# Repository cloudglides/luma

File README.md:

# Luma
It is a 75% layout, mechanical keyboard!  

I made this project because I wanna checkout how matrixs work. This would be my first keyboard!

### PCB
The PCB is designed to be compatible with Cherry MX switches and features hot-swappable kalih sockets.
| Schematics |
| --- |
| | 

| PCB (All Layers)|
| --- |
|  |

## Case

The case is designed to be 3D printed!

| Case top view|
| --- |
|  |

| Case bottom View|
| --- |
|  |

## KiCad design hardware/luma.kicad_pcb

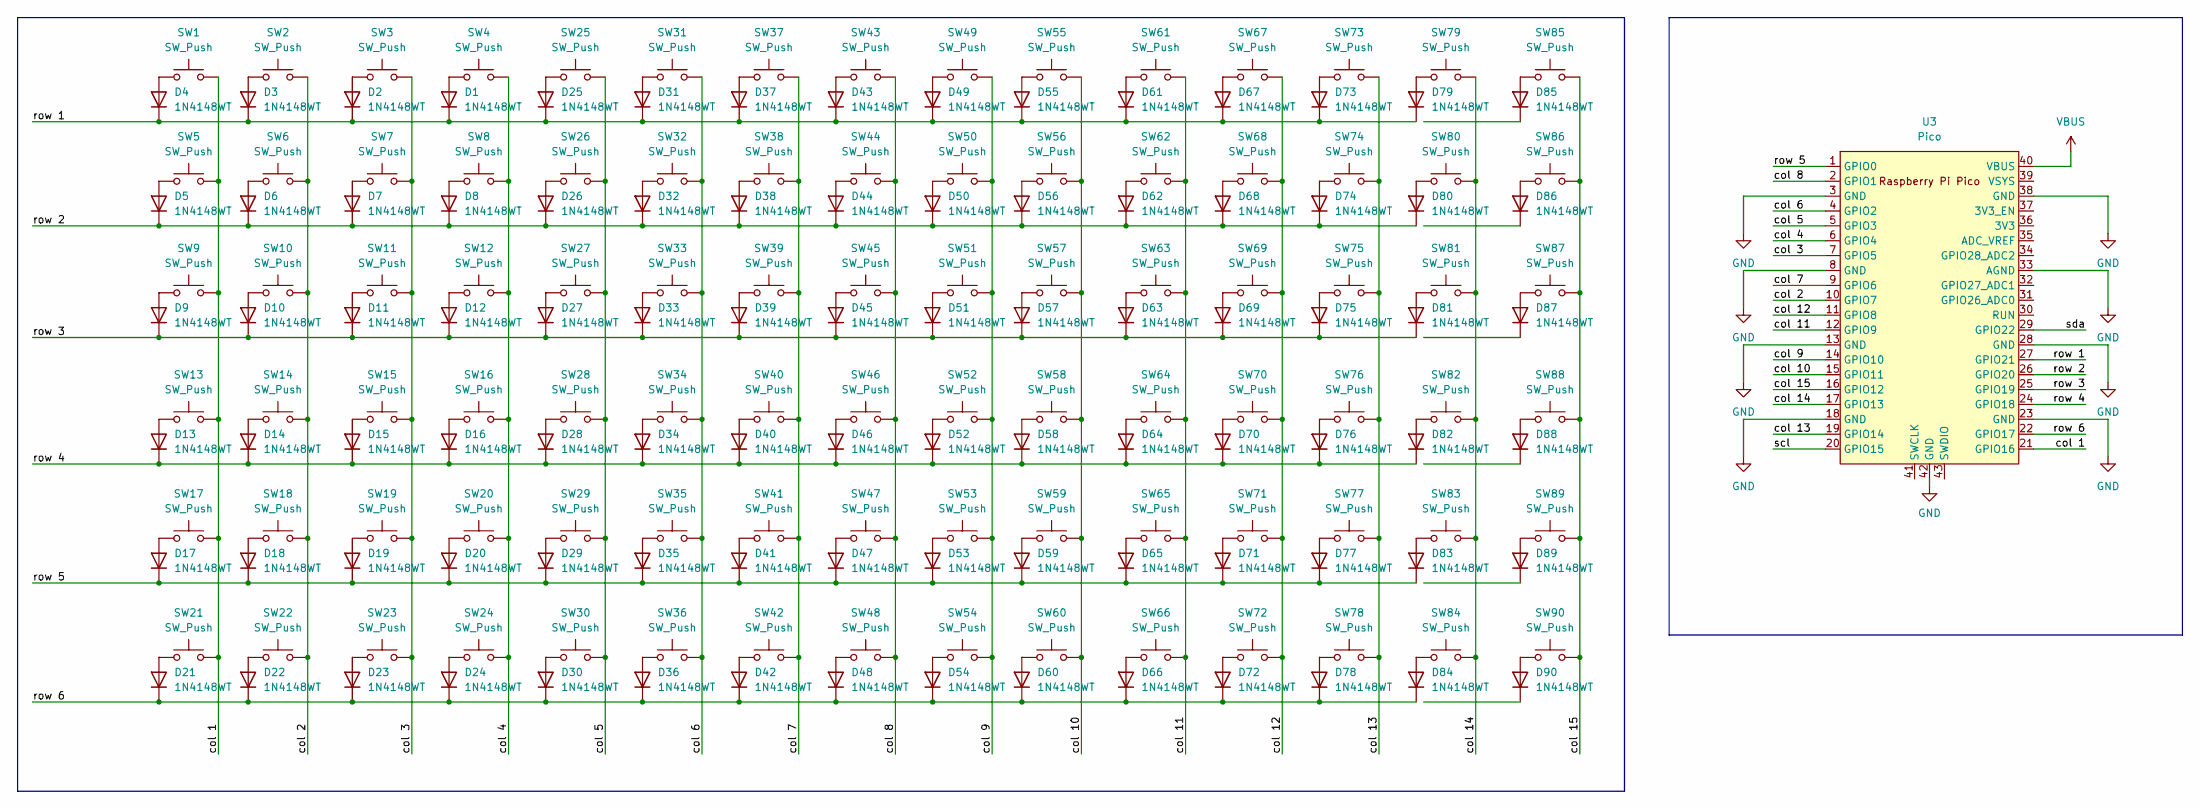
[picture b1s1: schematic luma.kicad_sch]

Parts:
D1, D2, D3, D4, D5, D6, D7, D8, D9, D10, D11, D12, D13, D14, D15, D16, D17, D18, D19, D20, D21, D22, D23, D24, D25, D26, D27, D28, D29, D30, D31, D32, D33, D34, D35, D36, D37, D38, D39, D40, D41, D42, D43, D44, D45, D46, D47, D48, D49, D50, D51, D52, D53, D54, D55, D56, D57, D58, D59, D60, D61, D62, D63, D64, D65, D66, D67, D68, D69, D70, D71, D72, D73, D74, D75, D76, D77, D78, D79, D80, D81, D82, D83, D84, D85, D86, D87, D88, D89, D90: 1N4148WT; D_SOD-523
SW1, SW2, SW3, SW4, SW5, SW6, SW7, SW8, SW9, SW10, SW11, SW12, SW13, SW14, SW15, SW16, SW17, SW18, SW19, SW20, SW21, SW22, SW23, SW24, SW25, SW26, SW27, SW28, SW29, SW31, SW32, SW33, SW34, SW35, SW36, SW37, SW38, SW39, SW40, SW41, SW42, SW43, SW44, SW45, SW46, SW47, SW48, SW49, SW50, SW51, SW52, SW53, SW54, SW55, SW56, SW57, SW58, SW60, SW62, SW63, SW64, SW65, SW66, SW67, SW68, SW69, SW70, SW71, SW72, SW73, SW74, SW75, SW76, SW77, SW79, SW80, SW81, SW82, SW83, SW84, SW85, SW86, SW87, SW88, SW89, SW90: SW_Push; SW_Cherry_MX_1.00u_PCB
SW30, SW59, SW61: SW_Push; SW_Cherry_MX_2.00u_PCB
SW78: SW_Push; SW_Cherry_MX_6.25u_PCB
U3: Pico; RPi_Pico_SMD_TH

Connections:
/col 1: SW1.2, SW5.2, SW9.2, SW13.2, SW17.2, SW21.2, U3.21 (GPIO16)
/col 2: SW2.2, SW6.2, SW10.2, SW14.2, SW18.2, SW22.2, U3.10 (GPIO7)
/col 3: SW3.2, SW7.2, SW11.2, SW15.2, SW19.2, SW23.2, U3.7 (GPIO5)
/col 4: SW4.2, SW8.2, SW12.2, SW16.2, SW20.2, SW24.2, U3.6 (GPIO4)
/col 5: SW25.2, SW26.2, SW27.2, SW28.2, SW29.2, SW30.2, U3.5 (GPIO3)
/col 6: SW31.2, SW32.2, SW33.2, SW34.2, SW35.2, SW36.2, U3.4 (GPIO2)
/col 7: SW37.2, SW38.2, SW39.2, SW40.2, SW41.2, SW42.2, U3.9 (GPIO6)
/col 8: SW43.2, SW44.2, SW45.2, SW46.2, SW47.2, SW48.2, U3.2 (GPIO1)
/col 9: SW49.2, SW50.2, SW51.2, SW52.2, SW53.2, SW54.2, U3.14 (GPIO10)
/col 10: SW55.2, SW56.2, SW57.2, SW58.2, SW59.2, SW60.2, U3.15 (GPIO11)
/col 11: SW61.2, SW62.2, SW63.2, SW64.2, SW65.2, SW66.2, U3.12 (GPIO9)
/col 12: SW67.2, SW68.2, SW69.2, SW70.2, SW71.2, SW72.2, U3.11 (GPIO8)
/col 13: SW73.2, SW74.2, SW75.2, SW76.2, SW77.2, SW78.2, U3.19 (GPIO14)
/col 14: SW79.2, SW80.2, SW81.2, SW82.2, SW83.2, SW84.2, U3.17 (GPIO13)
/col 15: SW85.2, SW86.2, SW87.2, SW88.2, SW89.2, SW90.2, U3.16 (GPIO12)
/row 1: D1.1 (K), D2.1 (K), D3.1 (K), D4.1 (K), D25.1 (K), D31.1 (K), D37.1 (K), D43.1 (K), D49.1 (K), D55.1 (K), D61.1 (K), D67.1 (K), D73.1 (K), D79.1 (K), U3.27 (GPIO21)
/row 2: D5.1 (K), D6.1 (K), D7.1 (K), D8.1 (K), D26.1 (K), D32.1 (K), D38.1 (K), D44.1 (K), D50.1 (K), D56.1 (K), D62.1 (K), D68.1 (K), D74.1 (K), D80.1 (K), U3.26 (GPIO20)
/row 3: D9.1 (K), D10.1 (K), D11.1 (K), D12.1 (K), D27.1 (K), D33.1 (K), D39.1 (K), D45.1 (K), D51.1 (K), D57.1 (K), D63.1 (K), D69.1 (K), D75.1 (K), D81.1 (K), U3.25 (GPIO19)
/row 4: D13.1 (K), D14.1 (K), D15.1 (K), D16.1 (K), D28.1 (K), D34.1 (K), D40.1 (K), D46.1 (K), D52.1 (K), D58.1 (K), D64.1 (K), D70.1 (K), D76.1 (K), D82.1 (K), U3.24 (GPIO18)
/row 5: D17.1 (K), D18.1 (K), D19.1 (K), D20.1 (K), D29.1 (K), D35.1 (K), D41.1 (K), D47.1 (K), D53.1 (K), D59.1 (K), D65.1 (K), D71.1 (K), D77.1 (K), D83.1 (K), U3.1 (GPIO0)
/row 6: D21.1 (K), D22.1 (K), D23.1 (K), D24.1 (K), D30.1 (K), D36.1 (K), D42.1 (K), D48.1 (K), D54.1 (K), D60.1 (K), D66.1 (K), D72.1 (K), D78.1 (K), D84.1 (K), U3.22 (GPIO17)
/scl: U3.20 (GPIO15)
/sda: U3.29 (GPIO22)
GND: U3.3 (GND), U3.8 (GND), U3.13 (GND), U3.18 (GND), U3.23 (GND), U3.28 (GND), U3.33 (AGND), U3.38 (GND), U3.42 (GND)
unnamed: D1.2 (A), SW4.1
unnamed: D2.2 (A), SW3.1
unnamed: D3.2 (A), SW2.1
unnamed: D4.2 (A), SW1.1
unnamed: D5.2 (A), SW5.1
unnamed: D6.2 (A), SW6.1
unnamed: D7.2 (A), SW7.1
unnamed: D8.2 (A), SW8.1
unnamed: D9.2 (A), SW9.1
unnamed: D10.2 (A), SW10.1
unnamed: D11.2 (A), SW11.1
unnamed: D12.2 (A), SW12.1
unnamed: D13.2 (A), SW13.1
unnamed: D14.2 (A), SW14.1
unnamed: D15.2 (A), SW15.1
unnamed: D16.2 (A), SW16.1
unnamed: D17.2 (A), SW17.1
unnamed: D18.2 (A), SW18.1
unnamed: D19.2 (A), SW19.1
unnamed: D20.2 (A), SW20.1
unnamed: D21.2 (A), SW21.1
unnamed: D22.2 (A), SW22.1
unnamed: D23.2 (A), SW23.1
unnamed: D24.2 (A), SW24.1
unnamed: D25.2 (A), SW25.1
unnamed: D26.2 (A), SW26.1
unnamed: D27.2 (A), SW27.1
unnamed: D28.2 (A), SW28.1
unnamed: D29.2 (A), SW29.1
unnamed: D30.2 (A), SW30.1
unnamed: D31.2 (A), SW31.1
unnamed: D32.2 (A), SW32.1
unnamed: D33.2 (A), SW33.1
unnamed: D34.2 (A), SW34.1
unnamed: D35.2 (A), SW35.1
unnamed: D36.2 (A), SW36.1
unnamed: D37.2 (A), SW37.1
unnamed: D38.2 (A), SW38.1
unnamed: D39.2 (A), SW39.1
unnamed: D40.2 (A), SW40.1
unnamed: D41.2 (A), SW41.1
unnamed: D42.2 (A), SW42.1
unnamed: D43.2 (A), SW43.1
unnamed: D44.2 (A), SW44.1
unnamed: D45.2 (A), SW45.1
unnamed: D46.2 (A), SW46.1
unnamed: D47.2 (A), SW47.1
unnamed: D48.2 (A), SW48.1
unnamed: D49.2 (A), SW49.1
unnamed: D50.2 (A), SW50.1
unnamed: D51.2 (A), SW51.1
unnamed: D52.2 (A), SW52.1
unnamed: D53.2 (A), SW53.1
unnamed: D54.2 (A), SW54.1
unnamed: D55.2 (A), SW55.1
unnamed: D56.2 (A), SW56.1
unnamed: D57.2 (A), SW57.1
unnamed: D58.2 (A), SW58.1
unnamed: D59.2 (A), SW59.1
unnamed: D60.2 (A), SW60.1
unnamed: D61.2 (A), SW61.1
unnamed: D62.2 (A), SW62.1
unnamed: D63.2 (A), SW63.1
unnamed: D64.2 (A), SW64.1
unnamed: D65.2 (A), SW65.1
unnamed: D66.2 (A), SW66.1
unnamed: D67.2 (A), SW67.1
unnamed: D68.2 (A), SW68.1
unnamed: D69.2 (A), SW69.1
unnamed: D70.2 (A), SW70.1
unnamed: D71.2 (A), SW71.1
unnamed: D72.2 (A), SW72.1
unnamed: D73.2 (A), SW73.1
unnamed: D74.2 (A), SW74.1
unnamed: D75.2 (A), SW75.1
unnamed: D76.2 (A), SW76.1
unnamed: D77.2 (A), SW77.1
unnamed: D78.2 (A), SW78.1
unnamed: D79.2 (A), SW79.1
unnamed: D80.2 (A), SW80.1
unnamed: D81.2 (A), SW81.1
unnamed: D82.2 (A), SW82.1
unnamed: D83.2 (A), SW83.1
unnamed: D84.2 (A), SW84.1
unnamed: D85.2 (A), SW85.1
unnamed: D86.2 (A), SW86.1
unnamed: D87.2 (A), SW87.1
unnamed: D88.2 (A), SW88.1
unnamed: D89.2 (A), SW89.1
unnamed: D90.2 (A), SW90.1
VBUS: U3.40 (VBUS)

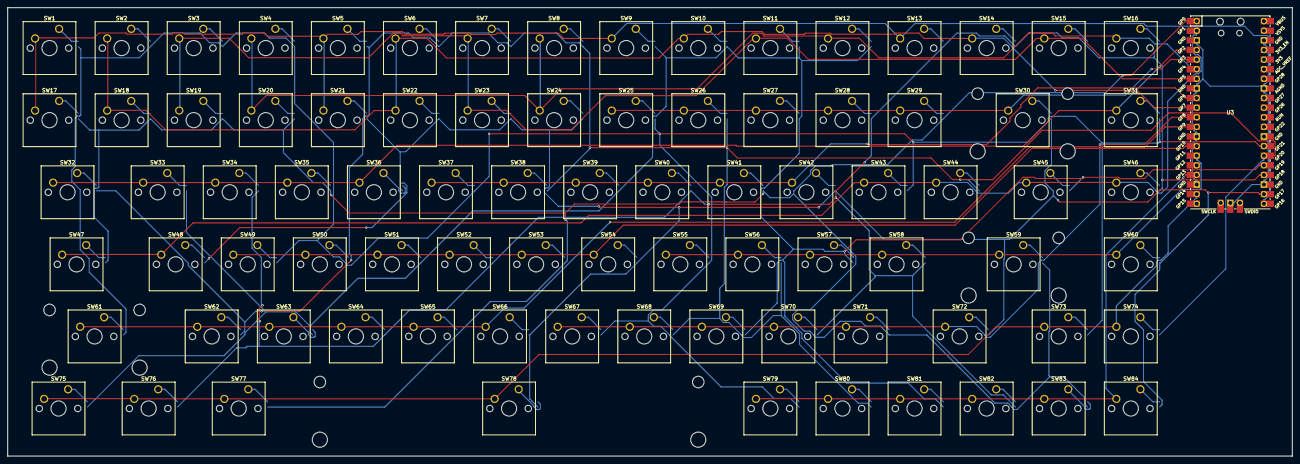
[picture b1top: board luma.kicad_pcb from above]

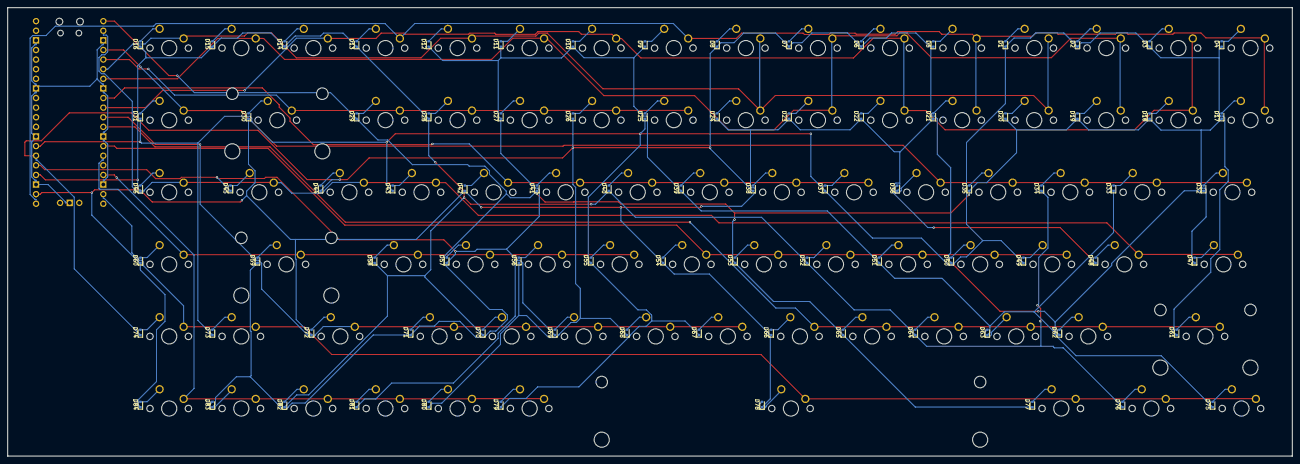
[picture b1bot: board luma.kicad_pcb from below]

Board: 2 copper layers, 339.5 x 118.5 mm, 169 parts (84 on the bottom side), 105 nets.

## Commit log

2026-04-21 inital commit
2026-04-21 update: readme
